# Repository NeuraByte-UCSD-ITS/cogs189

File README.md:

# **COGS 189 - BCI Project**  

This repository contains the code for our **COGS 189 Brain-Computer Interface (BCI) experiment**, where we map **action-based EEG signals and SSVEP** to real-time cursor control.  

### **Project Structure**  
- **`online` branch**: Handles real-time BCI implementation and cursor control mapping.  
- **`offline` branch**: Focuses on EEG signal preprocessing, transformation, and classification.  

### **Getting Started**  
1. Clone the repository:  
   ```bash
   git clone https://github.com/NeuraByte-UCSD-ITS/cogs189.git
   ```
2. Switch to the relevant branch:  
   ```bash
   git checkout online   # or git checkout offline
   ```
3. Stay updated with the latest changes:  
   ```bash
   git pull origin branch-name  # Replace 'branch-name' with online/offline/main
   ```

### **Contributing**  
1. Make changes and push to your branch:  
   ```bash
   git add .
   git commit -m "Your commit message"
   git push origin branch-name
   ```
2. Submit a pull request on GitHub to merge into `main`.  
3. Keep documentation updated for reproducibility.  

### **Team Members**  

| Name                  | PID        | Email             | Discord            | GitHub Username |
|-----------------------|-----------|-------------------|--------------------|-----------------|
| **Edwin Ruiz**        | A17136339 | e1ruiz@ucsd.edu   | ucsd_its_neuro     | NeuraByte-UCSD-ITS |
| **Vishal Patel**      | v7patel    | v7patel@ucsd.edu  | vishalp            | vip11017 |
| **Dante Testini**     | A16772108 | dtestini@ucsd.edu | dante.___          | Dante-t0 |
| **Nancy Shen**        | A17006379 | nshen@ucsd.edu    | nyzll              | nancyshenn |
| **Sarah R. Bulatao**  | A17239438 | sbulatao@ucsd.edu | 3ffulgentx#4449    | sbulatao |
| **Andy Huang**        | A17391626 | anh031@ucsd.edu   | nub6234            | anh1231 |

### **Project Resources**  

📄 **Team Documents (Proposal, Contract, Research Notes)**  
[**Google Docs - COGS 189 Team Documents**](https://docs.google.com/document/d/1kmoATubGGtCyLEcY0Lt7Y57b31m-O8rysbtMINhthrM/edit?usp=sharing)  

🌐 **Project Website (Introduction, Methods, Results)**  
[**Google Sites - COGS 189 BCI Project**](https://sites.google.com/d/1s-25WKa0uhgr7BEy_yGSoqZ5aTbzqCl3/p/1npJnzpZkbIYuBNoyv4HmWuREFpSlRTLe/edit?pli=1&authuser=2)

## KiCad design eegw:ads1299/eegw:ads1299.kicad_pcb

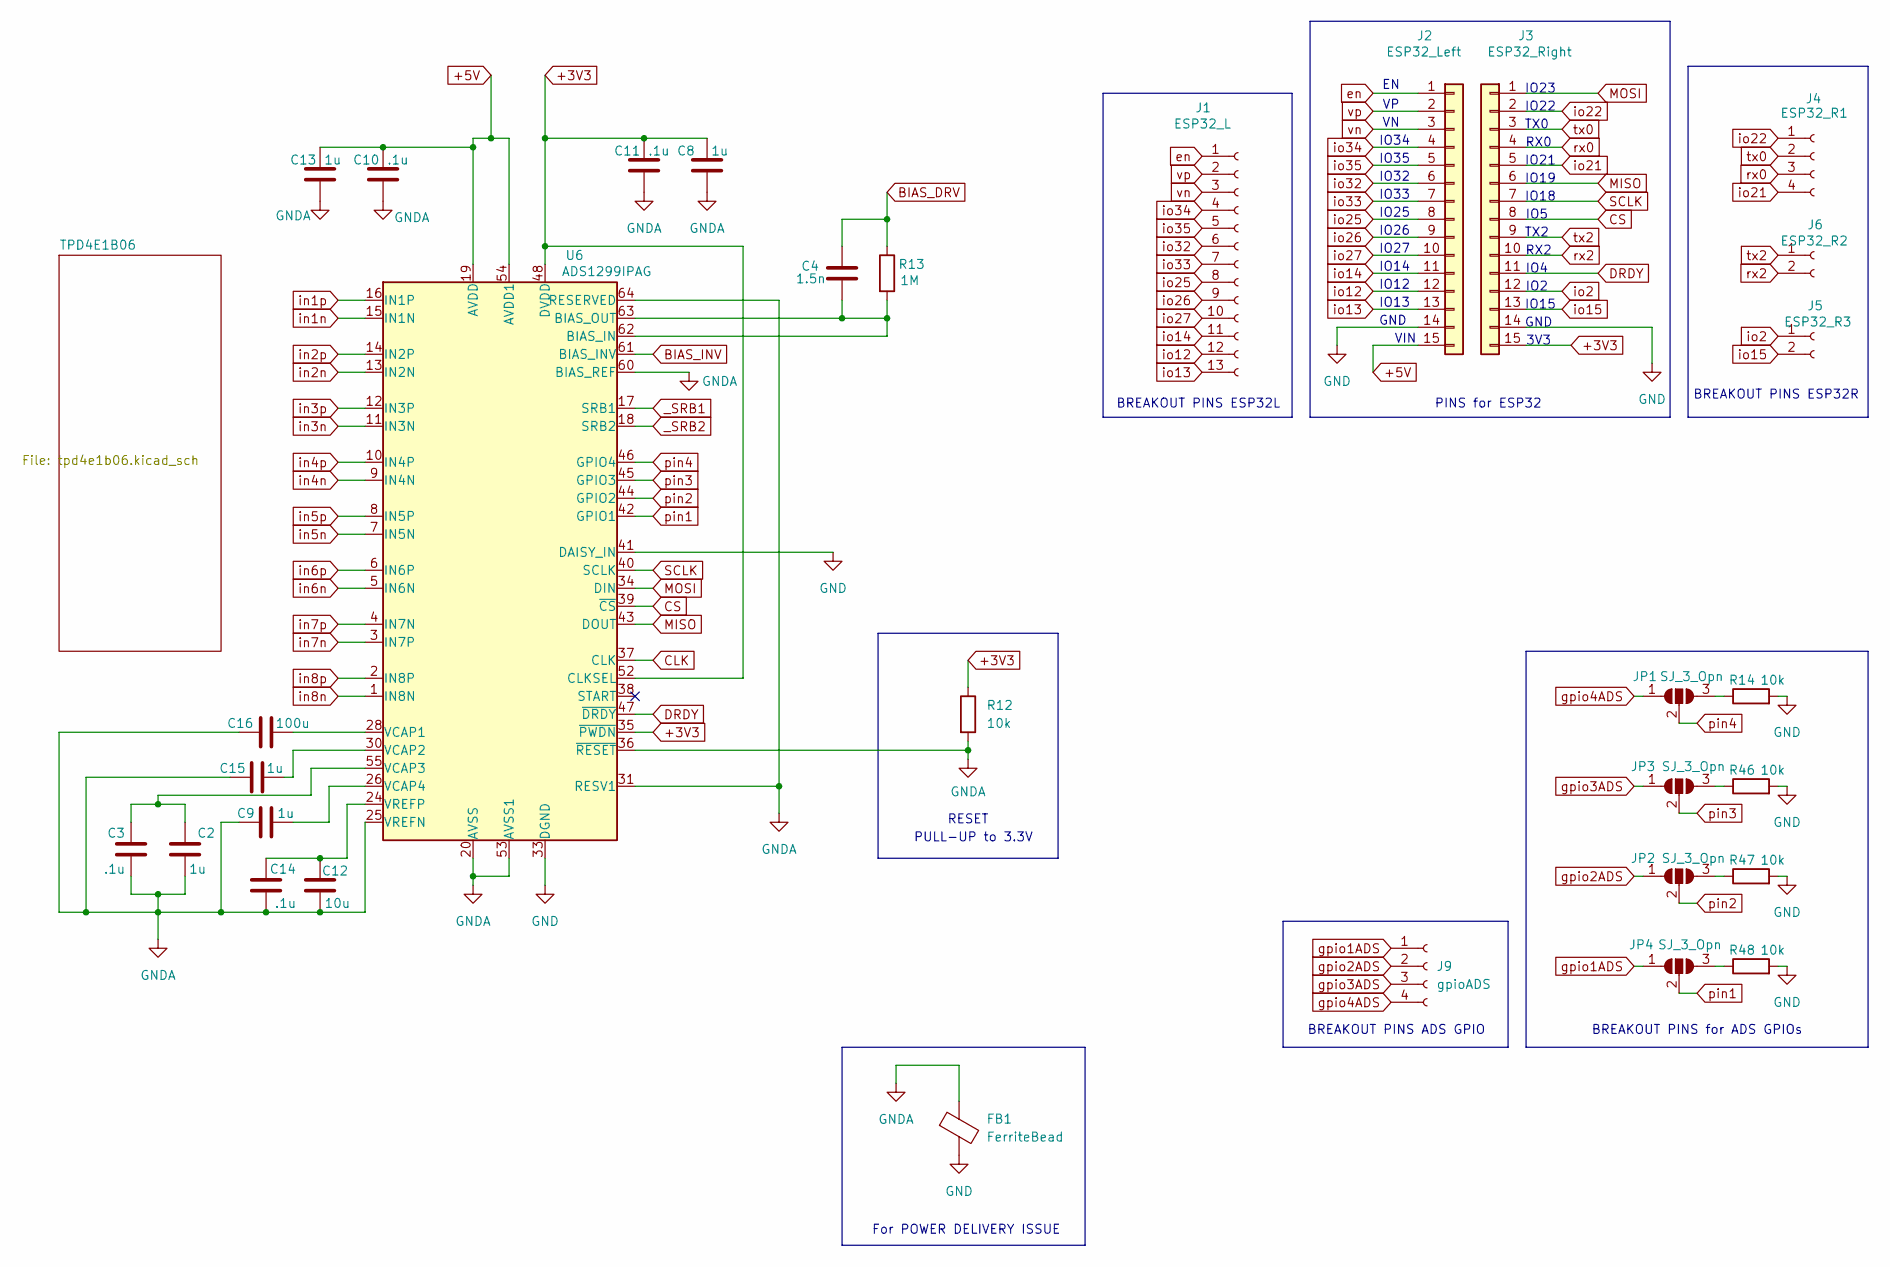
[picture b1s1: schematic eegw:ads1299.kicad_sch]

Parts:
C2, C8, C9, C13, C15: 1u; C_0603_1608Metric
C3, C10, C11, C14: .1u; C_0603_1608Metric
C4: 1.5n; C_0603_1608Metric
C12: 10u; C_0603_1608Metric
C16: 100u; C_0603_1608Metric
FB1: FerriteBead; L_0603_1608Metric
J1: ESP32_L; PinSocket_1x13_P2.54mm_Vertical
J2: ESP32_Left; PinSocket_1x15_P2.54mm_Vertical
J3: ESP32_Right; PinSocket_1x15_P2.54mm_Vertical
J4: ESP32_R1; PinSocket_1x04_P2.54mm_Vertical
J5: ESP32_R3; PinSocket_1x02_P2.54mm_Vertical
J6: ESP32_R2; PinSocket_1x02_P2.54mm_Vertical
J9: gpioADS; PinSocket_1x04_P2.54mm_Vertical
JP1, JP2, JP3, JP4: SJ_3_Opn; SolderJumper-3_P1.3mm_Open_RoundedPad1.0x1.5mm_NumberLabels
R12, R14, R46, R47, R48: 10k; R_0603_1608Metric
R13: 1M; R_0603_1608Metric
U6: ADS1299IPAG; TQFP-64_10x10mm_P0.5mm

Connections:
+3V3: C8.1, C11.1, J3.15, R12.1, U6.35 (~PWDN), U6.48 (DVDD), U6.50 (DVDD), U6.52 (CLKSEL)
+5V: C10.1, C13.1, J2.15, U6.19 (AVDD), U6.21 (AVDD), U6.22 (AVDD), U6.54 (AVDD1), U6.56 (AVDD), U6.59 (AVDD); also elsewhere on the board
BIAS_DRV: C4.1, R13.1; also elsewhere on the board
BIAS_INV: U6.61 (BIAS_INV)
CLK: U6.37 (CLK)
CS: J3.8, U6.39 (~CS)
DRDY: J3.11, U6.47 (~DRDY)
GND: FB1.2, J2.14, J3.14, R14.2, R46.2, R47.2, R48.2, U6.33 (DGND), U6.41 (DAISY_IN), U6.49 (DGND), U6.51 (DGND)
GNDA: C2.1, C3.1, C8.2, C9.1, C10.2, C11.2, C12.1, C13.2, C14.1, C15.1, C16.2, FB1.1, R12.2, U6.20 (AVSS), U6.23 (AVSS), U6.25 (VREFN), U6.31 (RESV1), U6.32 (AVSS), U6.36 (~RESET), U6.53 (AVSS1), U6.57 (AVSS), U6.58 (AVSS), U6.60 (BIAS_REF), U6.64 (RESERVED); also elsewhere on the board
MISO: J3.6, U6.43 (DOUT)
MOSI: J3.1, U6.34 (DIN)
unnamed: JP1.3 (B), R14.1
unnamed: JP2.3 (B), R47.1
unnamed: JP3.3 (B), R46.1
unnamed: JP4.3 (B), R48.1
unnamed: C4.2, R13.2, U6.62 (BIAS_IN), U6.63 (BIAS_OUT)
unnamed: C16.1, U6.28 (VCAP1)
unnamed: C15.2, U6.30 (VCAP2)
unnamed: C2.2, C3.2, U6.55 (VCAP3)
unnamed: C9.2, U6.26 (VCAP4)
unnamed: C12.2, C14.2, U6.24 (VREFP)
SCLK: J3.7, U6.40 (SCLK)
_SRB1: U6.17 (SRB1); also elsewhere on the board
_SRB2: U6.18 (SRB2); also elsewhere on the board
en: J1.1, J2.1
gpio1ADS: J9.1, JP4.1 (A)
gpio2ADS: J9.2, JP2.1 (A)
gpio3ADS: J9.3, JP3.1 (A)
gpio4ADS: J9.4, JP1.1 (A)
in1n: U6.15 (IN1N); also elsewhere on the board
in1p: U6.16 (IN1P); also elsewhere on the board
in2n: U6.13 (IN2N); also elsewhere on the board
in2p: U6.14 (IN2P); also elsewhere on the board
in3n: U6.11 (IN3N); also elsewhere on the board
in3p: U6.12 (IN3P); also elsewhere on the board
in4n: U6.9 (IN4N); also elsewhere on the board
in4p: U6.10 (IN4P); also elsewhere on the board
in5n: U6.7 (IN5N); also elsewhere on the board
in5p: U6.8 (IN5P); also elsewhere on the board
in6n: U6.5 (IN6N); also elsewhere on the board
in6p: U6.6 (IN6P); also elsewhere on the board
in7n: U6.3 (IN7P); also elsewhere on the board
in7p: U6.4 (IN7N); also elsewhere on the board
in8n: U6.1 (IN8N); also elsewhere on the board
in8p: U6.2 (IN8P); also elsewhere on the board
io2: J3.12, J5.1
io12: J1.12, J2.12
io13: J1.13, J2.13
io14: J1.11, J2.11
io15: J3.13, J5.2
io21: J3.5, J4.4
io22: J3.2, J4.1
io25: J1.8, J2.8
io26: J1.9, J2.9
io27: J1.10, J2.10
io32: J1.6, J2.6
io33: J1.7, J2.7
io34: J1.4, J2.4
io35: J1.5, J2.5
pin1: JP4.2 (C), U6.42 (GPIO1)
pin2: JP2.2 (C), U6.44 (GPIO2)
pin3: JP3.2 (C), U6.45 (GPIO3)
pin4: JP1.2 (C), U6.46 (GPIO4)
rx0: J3.4, J4.3
rx2: J3.10, J6.2
tx0: J3.3, J4.2
tx2: J3.9, J6.1
vn: J1.3, J2.3
vp: J1.2, J2.2

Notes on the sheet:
IO19
IO21
IO4
For POWER DELIVERY ISSUE
IO15
IO34
IO33
IO26
PINS for ESP32
TX0
BREAKOUT PINS ESP32R
IO2
IO18
IO27
BREAKOUT PINS ESP32L
TX2
IO13
IO25
GND
BREAKOUT PINS for ADS GPIOs
IO32
IO22
RX0
IO23
RESET
IO35
PULL-UP to 3.3V
VIN
IO14
IO5
BREAKOUT PINS ADS GPIO
3V3
RX2
IO12

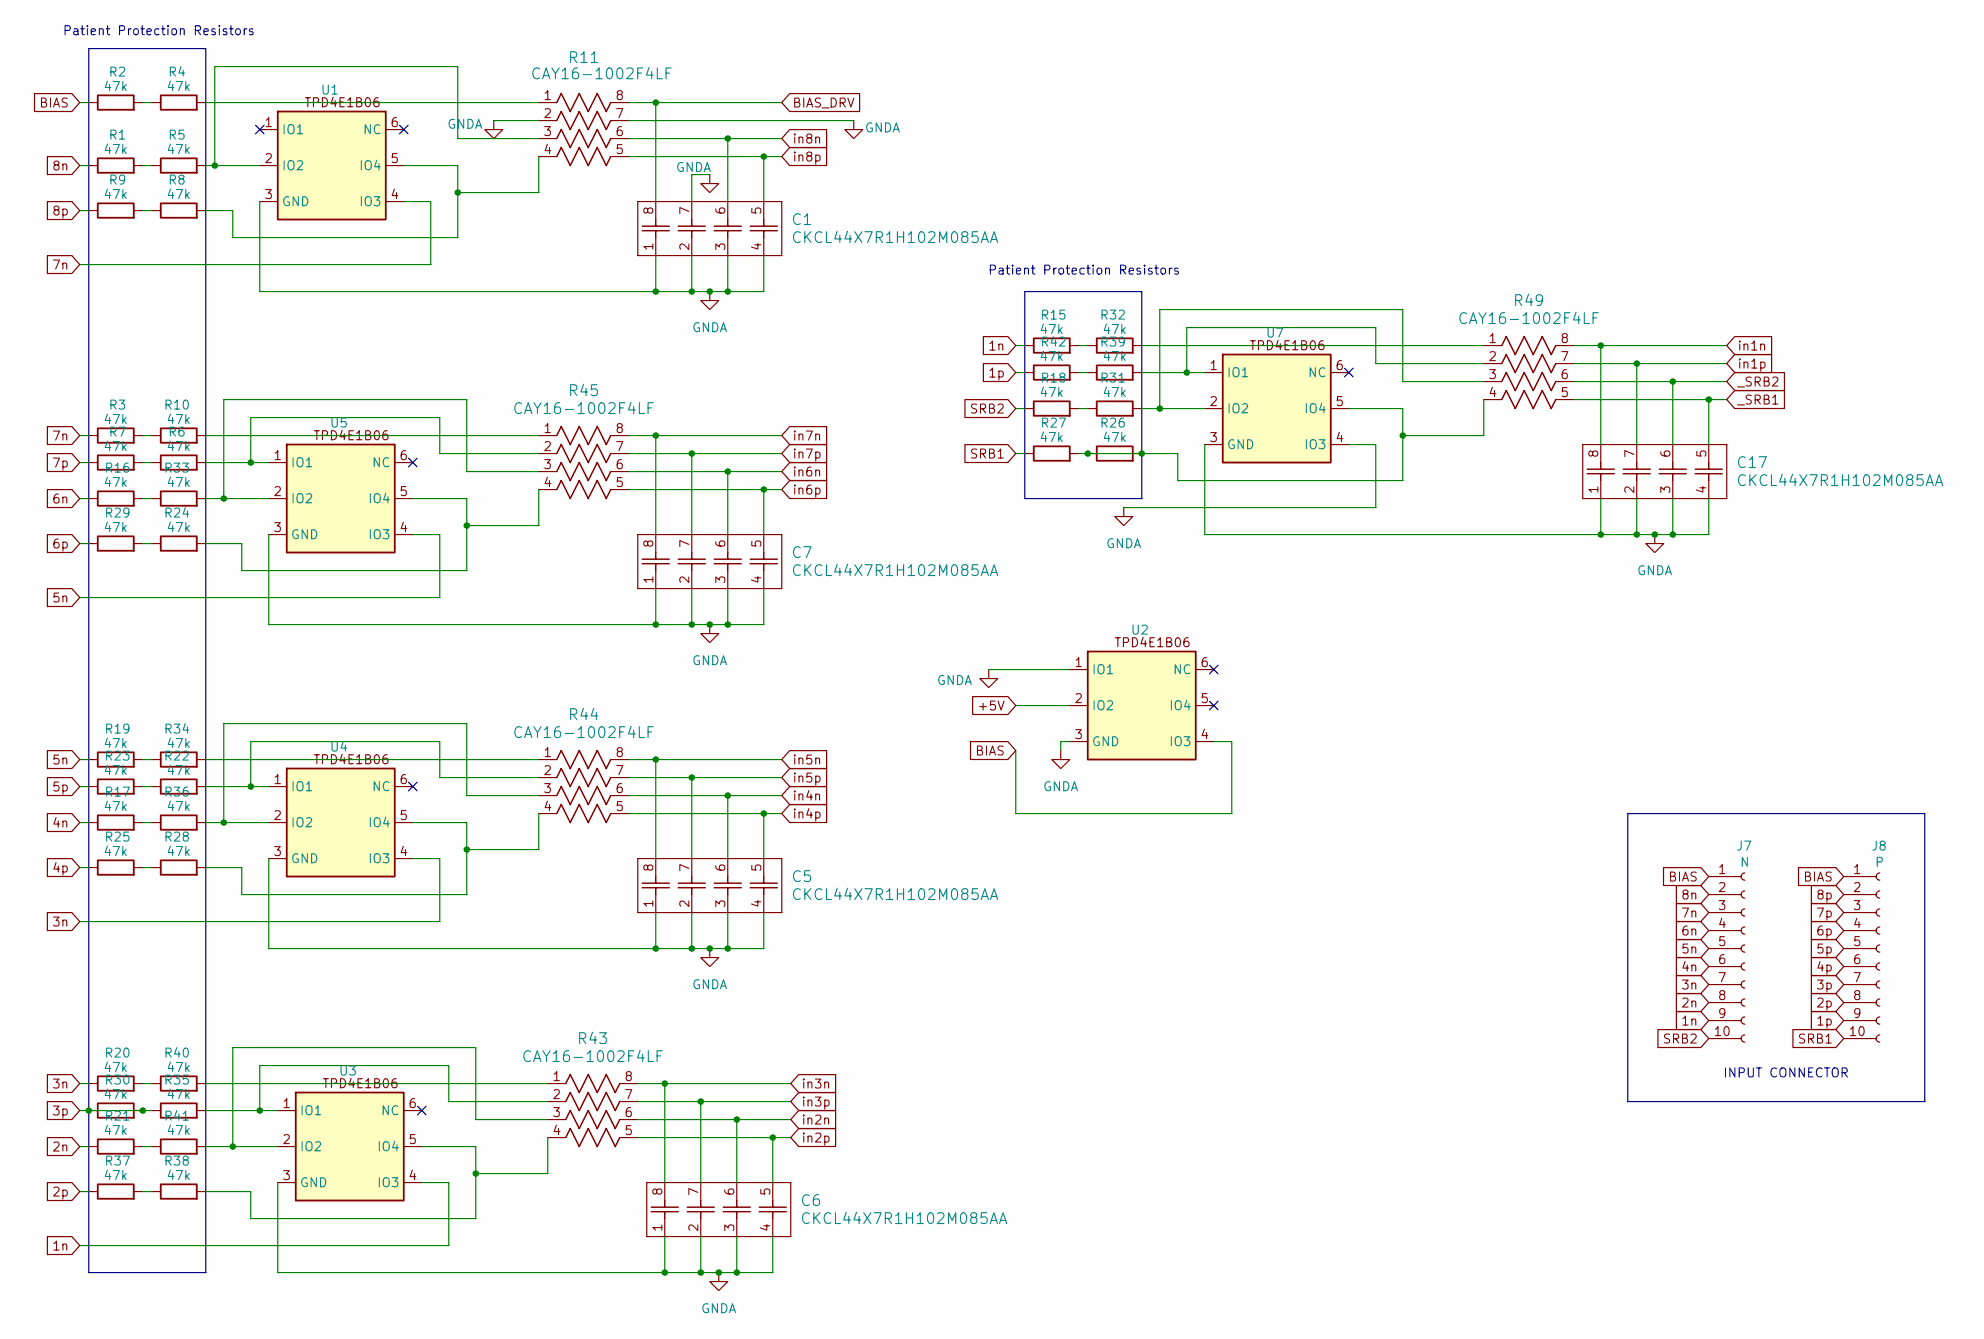
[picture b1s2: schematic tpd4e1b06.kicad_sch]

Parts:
C1, C5, C6, C7, C17: CKCL44X7R1H102M085AA; CKCL44_TDK
J7: N; PinSocket_1x10_P2.54mm_Vertical
J8: P; PinSocket_1x10_P2.54mm_Vertical
R1, R2, R3, R4, R5, R6, R7, R8, R9, R10, R15, R16, R17, R18, R19, R20, R21, R22, R23, R24, R25, R26, R27, R28, R29, R30, R31, R32, R33, R34, R35, R36, R37, R38, R39, R40, R41, R42: 47k; R_0603_1608Metric
R11, R43, R44, R45, R49: CAY16-1002F4LF; BO_CAY16
U1, U2, U3, U4, U5, U7: SOT-363_SC-70-6

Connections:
1n: J7.9, R15.1, U3.4 (IO3)
1p: J8.9, R42.1
2n: J7.8, R21.1
2p: J8.8, R37.1
3n: J7.7, R20.1, U4.4 (IO3)
3p: J8.7, R30.1, R30.2, R35.1
4n: J7.6, R17.1
4p: J8.6, R25.1
5n: J7.5, R19.1, U5.4 (IO3)
5p: J8.5, R23.1
6n: J7.4, R16.1
6p: J8.4, R29.1
7n: J7.3, R3.1, U1.4 (IO3)
7p: J8.3, R7.1
8n: J7.2, R1.1
8p: J8.2, R9.1
+5V: U2.2 (IO2); also elsewhere on the board
BIAS: J7.1, J8.1, R2.1, U2.4 (IO3)
BIAS_DRV: C1.8, R11.8; also elsewhere on the board
GNDA: C1.1, C1.2, C1.3, C1.4, C1.7, C5.1, C5.2, C5.3, C5.4, C6.1, C6.2, C6.3, C6.4, C7.1, C7.2, C7.3, C7.4, C17.1, C17.2, C17.3, C17.4, R11.2, R11.7, U1.3 (GND), U2.1 (IO1), U2.3 (GND), U3.3 (GND), U4.3 (GND), U5.3 (GND), U7.3 (GND), U7.4 (IO3); also elsewhere on the board
unnamed: R1.2, R5.1
unnamed: R2.2, R4.1
unnamed: R6.1, R7.2
unnamed: R8.1, R9.2
unnamed: R3.2, R10.1
unnamed: R10.2, R45.1
unnamed: R4.2, R11.1
unnamed: R15.2, R32.1
unnamed: R16.2, R33.1
unnamed: R17.2, R36.1
unnamed: R18.2, R31.1
unnamed: R19.2, R34.1
unnamed: R20.2, R40.1
unnamed: R21.2, R41.1
unnamed: R22.1, R23.2
unnamed: R24.1, R29.2
unnamed: R25.2, R28.1
unnamed: R32.2, R49.1
unnamed: R34.2, R44.1
unnamed: R37.2, R38.1
unnamed: R39.1, R42.2
unnamed: R40.2, R43.1
unnamed: R5.2, R11.3, U1.2 (IO2)
unnamed: R8.2, R11.4, U1.5 (IO4)
unnamed: R35.2, R43.2, U3.1 (IO1)
unnamed: R41.2, R43.3, U3.2 (IO2)
unnamed: R38.2, R43.4, U3.5 (IO4)
unnamed: R22.2, R44.2, U4.1 (IO1)
unnamed: R36.2, R44.3, U4.2 (IO2)
unnamed: R28.2, R44.4, U4.5 (IO4)
unnamed: R6.2, R45.2, U5.1 (IO1)
unnamed: R33.2, R45.3, U5.2 (IO2)
unnamed: R24.2, R45.4, U5.5 (IO4)
unnamed: R39.2, R49.2, U7.1 (IO1)
unnamed: R31.2, R49.3, U7.2 (IO2)
unnamed: R26.1, R26.2, R27.2, R49.4, U7.5 (IO4)
SRB1: J8.10, R27.1
SRB2: J7.10, R18.1
_SRB1: C17.5, R49.5; also elsewhere on the board
_SRB2: C17.6, R49.6; also elsewhere on the board
in1n: C17.8, R49.8; also elsewhere on the board
in1p: C17.7, R49.7; also elsewhere on the board
in2n: C6.6, R43.6; also elsewhere on the board
in2p: C6.5, R43.5; also elsewhere on the board
in3n: C6.8, R43.8; also elsewhere on the board
in3p: C6.7, R43.7; also elsewhere on the board
in4n: C5.6, R44.6; also elsewhere on the board
in4p: C5.5, R44.5; also elsewhere on the board
in5n: C5.8, R44.8; also elsewhere on the board
in5p: C5.7, R44.7; also elsewhere on the board
in6n: C7.6, R45.6; also elsewhere on the board
in6p: C7.5, R45.5; also elsewhere on the board
in7n: C7.8, R45.8; also elsewhere on the board
in7p: C7.7, R45.7; also elsewhere on the board
in8n: C1.6, R11.6; also elsewhere on the board
in8p: C1.5, R11.5; also elsewhere on the board

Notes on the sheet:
Patient Protection Resistors
INPUT CONNECTOR

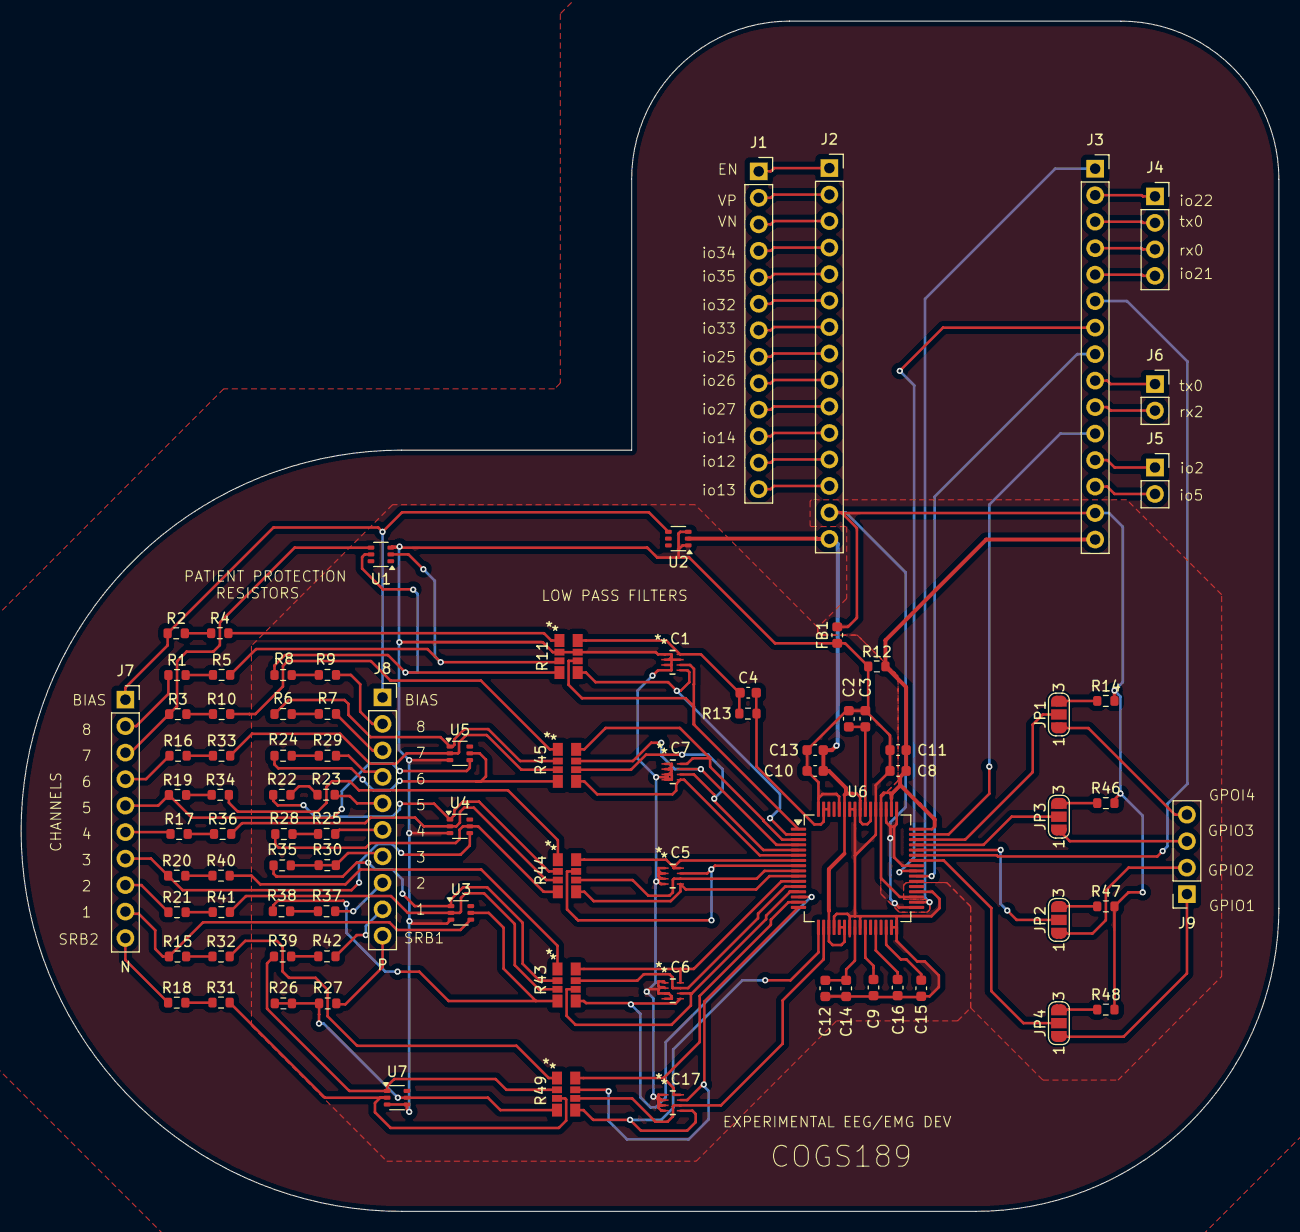
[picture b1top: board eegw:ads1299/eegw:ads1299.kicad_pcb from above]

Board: 2 copper layers, 120.6 x 114.1 mm, 87 parts (0 on the bottom side), 122 nets.

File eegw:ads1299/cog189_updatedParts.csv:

"Reference","Value","Datasheet","Footprint","Qty","DNP"
"C1,C5,C6,C7,C17","CKCL44X7R1H102M085AA","CKCL44X7R1H102M085AA","Capacitor_SMD:CKCL44_TDK","5",""
"C2,C8,C9,C13,C15","1u","~","Capacitor_SMD:C_0603_1608Metric","5",""
"C3,C10,C11,C14",".1u","~","Capacitor_SMD:C_0603_1608Metric","4",""
"C4","1.5n","~","Capacitor_SMD:C_0603_1608Metric","1",""
"C12","10u","~","Capacitor_SMD:C_0603_1608Metric","1",""
"C16","100u","~","Capacitor_SMD:CAPC_2012X145N Metric","1",""
"FB1","FerriteBead","~","Inductor_SMD:L_0603_1608Metric","1",""
"J1","ESP32_L","~","Connector_PinSocket_2.54mm:PinSocket_1x13_P2.54mm_Vertical","1",""
"J2","ESP32_Left","~","Connector_PinSocket_2.54mm:PinSocket_1x15_P2.54mm_Vertical","1",""
"J3","ESP32_Right","~","Connector_PinSocket_2.54mm:PinSocket_1x15_P2.54mm_Vertical","1",""
"J4","ESP32_R1","~","Connector_PinSocket_2.54mm:PinSocket_1x04_P2.54mm_Vertical","1",""
"J5","ESP32_R3","~","Connector_PinSocket_2.54mm:PinSocket_1x02_P2.54mm_Vertical","1",""
"J6","ESP32_R2","~","Connector_PinSocket_2.54mm:PinSocket_1x02_P2.54mm_Vertical","1",""
"J7","N","~","Connector_PinSocket_2.54mm:PinSocket_1x10_P2.54mm_Vertical","1",""
"J8","P","~","Connector_PinSocket_2.54mm:PinSocket_1x10_P2.54mm_Vertical","1",""
"J9","gpioADS","~","Connector_PinSocket_2.54mm:PinSocket_1x04_P2.54mm_Vertical","1",""
"R1,R2,R3,R4,R5,R6,R7,R8,R9,R10,R15,R16,R17,R18,R19,R20,R21,R22,R23,R24,R25,R26,R27,R28,R29,R30,R31,R32,R33,R34,R35,R36,R37,R38,R39,R40,R41,R42","47k","~","Resistor_SMD:R_0603_1608Metric","38",""
"R11,R43,R44,R45,R49","CAY16-1002F4LF","CAY16-1002F4LF","RF:BO_CAY16","5",""
"R12,R14,R46,R47,R48","10k","~","Resistor_SMD:R_0603_1608Metric","5",""
"R13","1M","~","Resistor_SMD:R_0603_1608Metric","1",""
"U1,U2,U3,U4,U5,U7","~","https://www.ti.com/lit/ds/symlink/tpd4e1b06.pdf?ts=173955177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","Package_TO_SOT_SMD:SOT-363_SC-70-6","6",""
"U6","ADS1299IPAG","https://www.ti.com/lit/ds/symlink/ads1299.pdf?ts=17389798611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","Package_QFP:TQFP-64_10x10mm_P0.5mm","1",""

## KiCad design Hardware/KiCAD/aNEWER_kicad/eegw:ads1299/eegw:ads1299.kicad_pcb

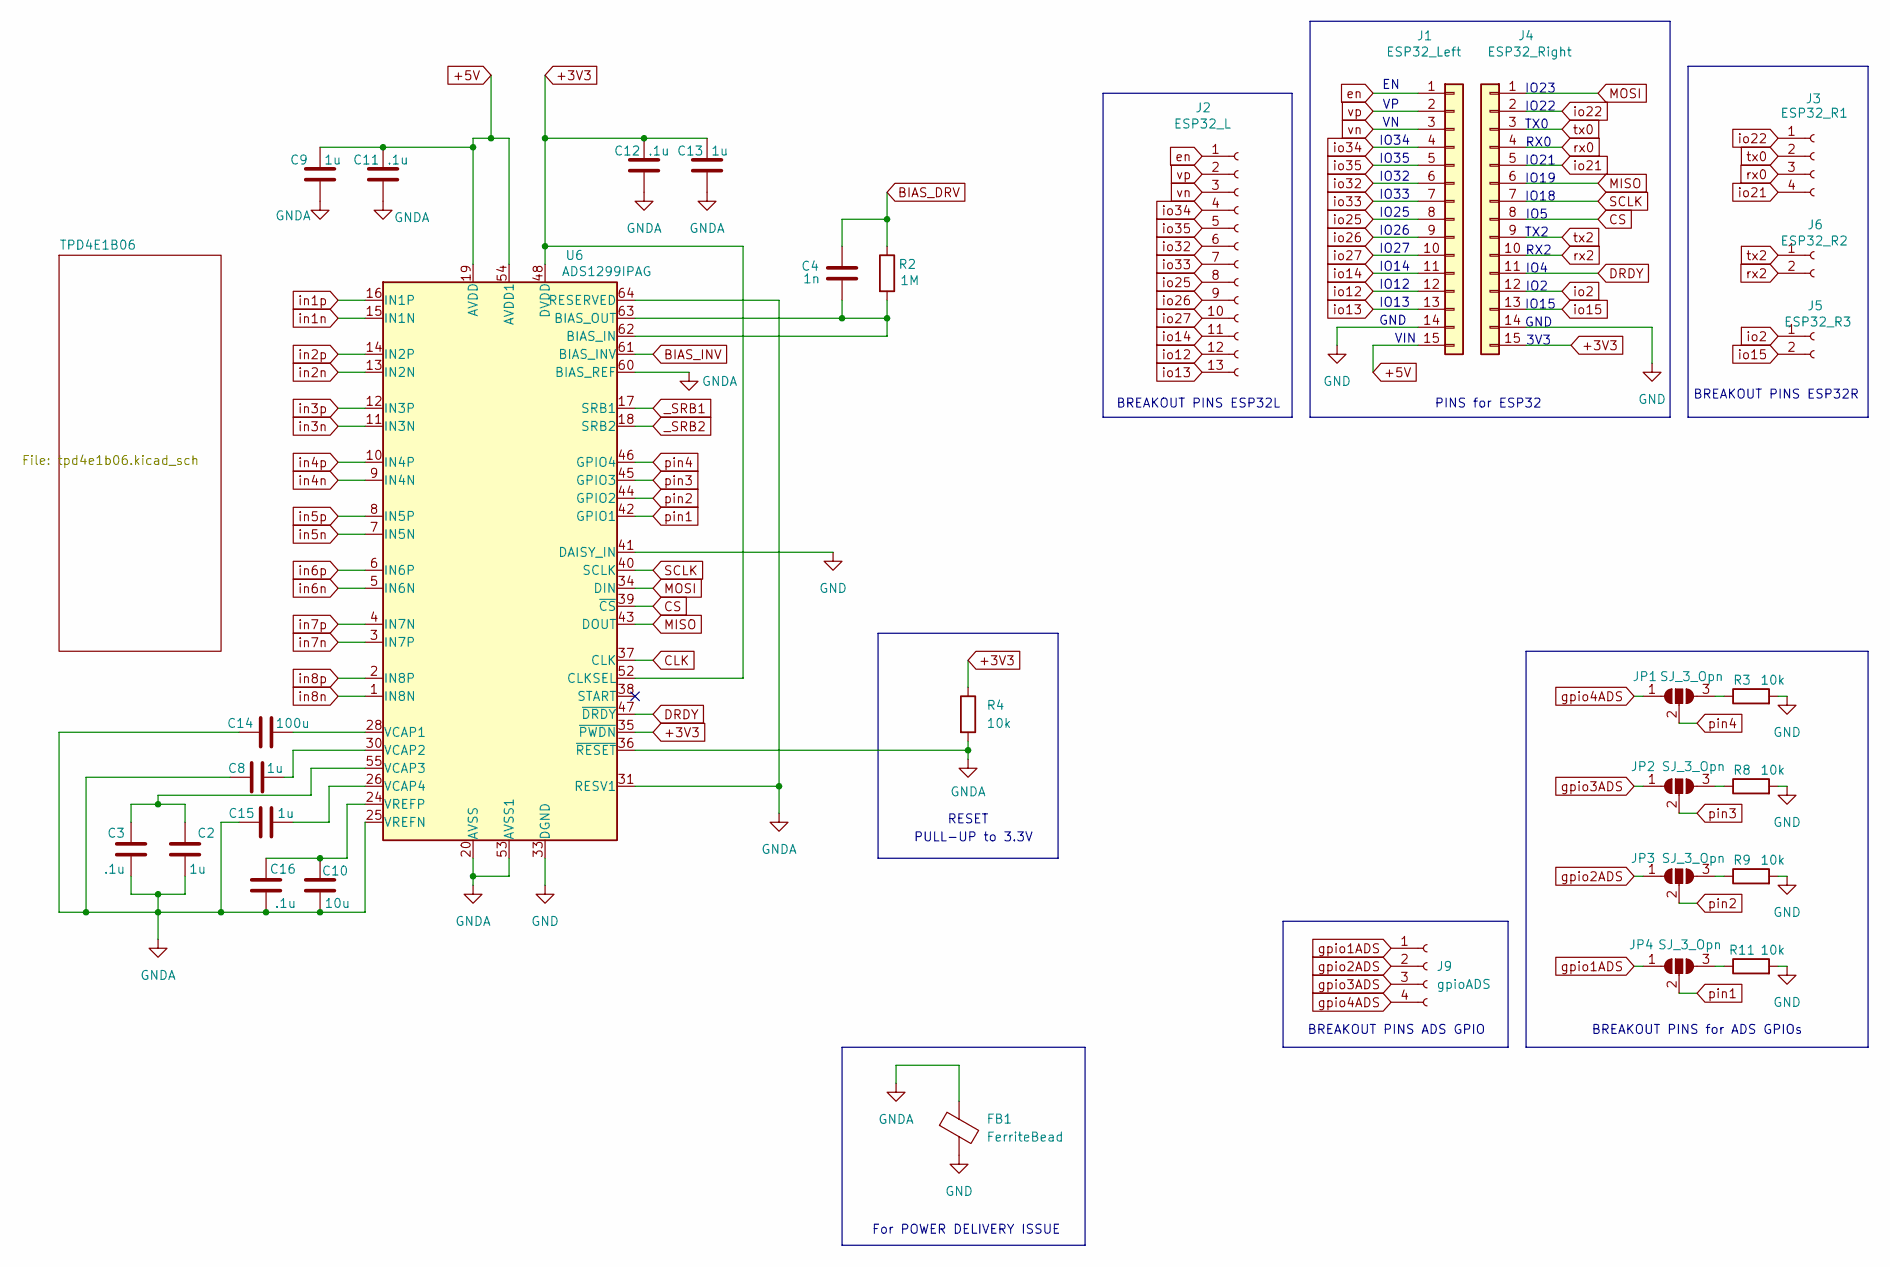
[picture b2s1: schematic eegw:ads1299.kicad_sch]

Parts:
C2, C8, C9, C13, C15: 1u; C_0603_1608Metric
C3, C11, C12, C16: .1u; C_0603_1608Metric
C4: 1n; C_0402_1005Metric
C10: 10u; C_0603_1608Metric
C14: 100u; CAPC_2012X145N Metric
FB1: FerriteBead; L_0603_1608Metric
J1: ESP32_Left; PinSocket_1x15_P2.54mm_Vertical
J2: ESP32_L; PinSocket_1x13_P2.54mm_Vertical
J3: ESP32_R1; PinSocket_1x04_P2.54mm_Vertical
J4: ESP32_Right; PinSocket_1x15_P2.54mm_Vertical
J5: ESP32_R3; PinSocket_1x02_P2.54mm_Vertical
J6: ESP32_R2; PinSocket_1x02_P2.54mm_Vertical
J9: gpioADS; PinSocket_1x04_P2.54mm_Vertical
JP1, JP2, JP3, JP4: SJ_3_Opn; SolderJumper-3_P1.3mm_Open_RoundedPad1.0x1.5mm_NumberLabels
R2: 1M; R_0603_1608Metric
R3, R4, R8, R9, R11: 10k; R_0603_1608Metric
U6: ADS1299IPAG; TQFP-64_10x10mm_P0.5mm

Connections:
+3V3: C12.1, C13.1, J4.15, R4.1, U6.35 (~PWDN), U6.48 (DVDD), U6.50 (DVDD), U6.52 (CLKSEL)
+5V: C9.1, C11.1, J1.15, U6.19 (AVDD), U6.21 (AVDD), U6.22 (AVDD), U6.54 (AVDD1), U6.56 (AVDD), U6.59 (AVDD); also elsewhere on the board
BIAS_DRV: C4.1, R2.1; also elsewhere on the board
BIAS_INV: U6.61 (BIAS_INV)
CLK: U6.37 (CLK)
CS: J4.8, U6.39 (~CS)
DRDY: J4.11, U6.47 (~DRDY)
GND: FB1.2, J1.14, J4.14, R3.2, R8.2, R9.2, R11.2, U6.33 (DGND), U6.41 (DAISY_IN), U6.49 (DGND), U6.51 (DGND)
GNDA: C2.1, C3.1, C8.1, C9.2, C10.1, C11.2, C12.2, C13.2, C14.2, C15.1, C16.1, FB1.1, R4.2, U6.20 (AVSS), U6.23 (AVSS), U6.25 (VREFN), U6.31 (RESV1), U6.32 (AVSS), U6.36 (~RESET), U6.53 (AVSS1), U6.57 (AVSS), U6.58 (AVSS), U6.60 (BIAS_REF), U6.64 (RESERVED); also elsewhere on the board
MISO: J4.6, U6.43 (DOUT)
MOSI: J4.1, U6.34 (DIN)
unnamed: JP1.3 (B), R3.1
unnamed: JP2.3 (B), R8.1
unnamed: JP3.3 (B), R9.1
unnamed: JP4.3 (B), R11.1
unnamed: C4.2, R2.2, U6.62 (BIAS_IN), U6.63 (BIAS_OUT)
unnamed: C14.1, U6.28 (VCAP1)
unnamed: C8.2, U6.30 (VCAP2)
unnamed: C2.2, C3.2, U6.55 (VCAP3)
unnamed: C15.2, U6.26 (VCAP4)
unnamed: C10.2, C16.2, U6.24 (VREFP)
SCLK: J4.7, U6.40 (SCLK)
_SRB1: U6.17 (SRB1); also elsewhere on the board
_SRB2: U6.18 (SRB2); also elsewhere on the board
en: J1.1, J2.1
gpio1ADS: J9.1, JP4.1 (A)
gpio2ADS: J9.2, JP3.1 (A)
gpio3ADS: J9.3, JP2.1 (A)
gpio4ADS: J9.4, JP1.1 (A)
in1n: U6.15 (IN1N); also elsewhere on the board
in1p: U6.16 (IN1P); also elsewhere on the board
in2n: U6.13 (IN2N); also elsewhere on the board
in2p: U6.14 (IN2P); also elsewhere on the board
in3n: U6.11 (IN3N); also elsewhere on the board
in3p: U6.12 (IN3P); also elsewhere on the board
in4n: U6.9 (IN4N); also elsewhere on the board
in4p: U6.10 (IN4P); also elsewhere on the board
in5n: U6.7 (IN5N); also elsewhere on the board
in5p: U6.8 (IN5P); also elsewhere on the board
in6n: U6.5 (IN6N); also elsewhere on the board
in6p: U6.6 (IN6P); also elsewhere on the board
in7n: U6.3 (IN7P); also elsewhere on the board
in7p: U6.4 (IN7N); also elsewhere on the board
in8n: U6.1 (IN8N); also elsewhere on the board
in8p: U6.2 (IN8P); also elsewhere on the board
io2: J4.12, J5.1
io12: J1.12, J2.12
io13: J1.13, J2.13
io14: J1.11, J2.11
io15: J4.13, J5.2
io21: J3.4, J4.5
io22: J3.1, J4.2
io25: J1.8, J2.8
io26: J1.9, J2.9
io27: J1.10, J2.10
io32: J1.6, J2.6
io33: J1.7, J2.7
io34: J1.4, J2.4
io35: J1.5, J2.5
pin1: JP4.2 (C), U6.42 (GPIO1)
pin2: JP3.2 (C), U6.44 (GPIO2)
pin3: JP2.2 (C), U6.45 (GPIO3)
pin4: JP1.2 (C), U6.46 (GPIO4)
rx0: J3.3, J4.4
rx2: J4.10, J6.2
tx0: J3.2, J4.3
tx2: J4.9, J6.1
vn: J1.3, J2.3
vp: J1.2, J2.2

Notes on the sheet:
IO19
IO21
IO4
For POWER DELIVERY ISSUE
IO15
IO34
IO33
IO26
PINS for ESP32
TX0
BREAKOUT PINS ESP32R
IO2
IO18
IO27
BREAKOUT PINS ESP32L
TX2
IO13
IO25
GND
BREAKOUT PINS for ADS GPIOs
IO32
IO22
RX0
IO23
RESET
IO35
PULL-UP to 3.3V
VIN
IO14
IO5
BREAKOUT PINS ADS GPIO
3V3
RX2
IO12

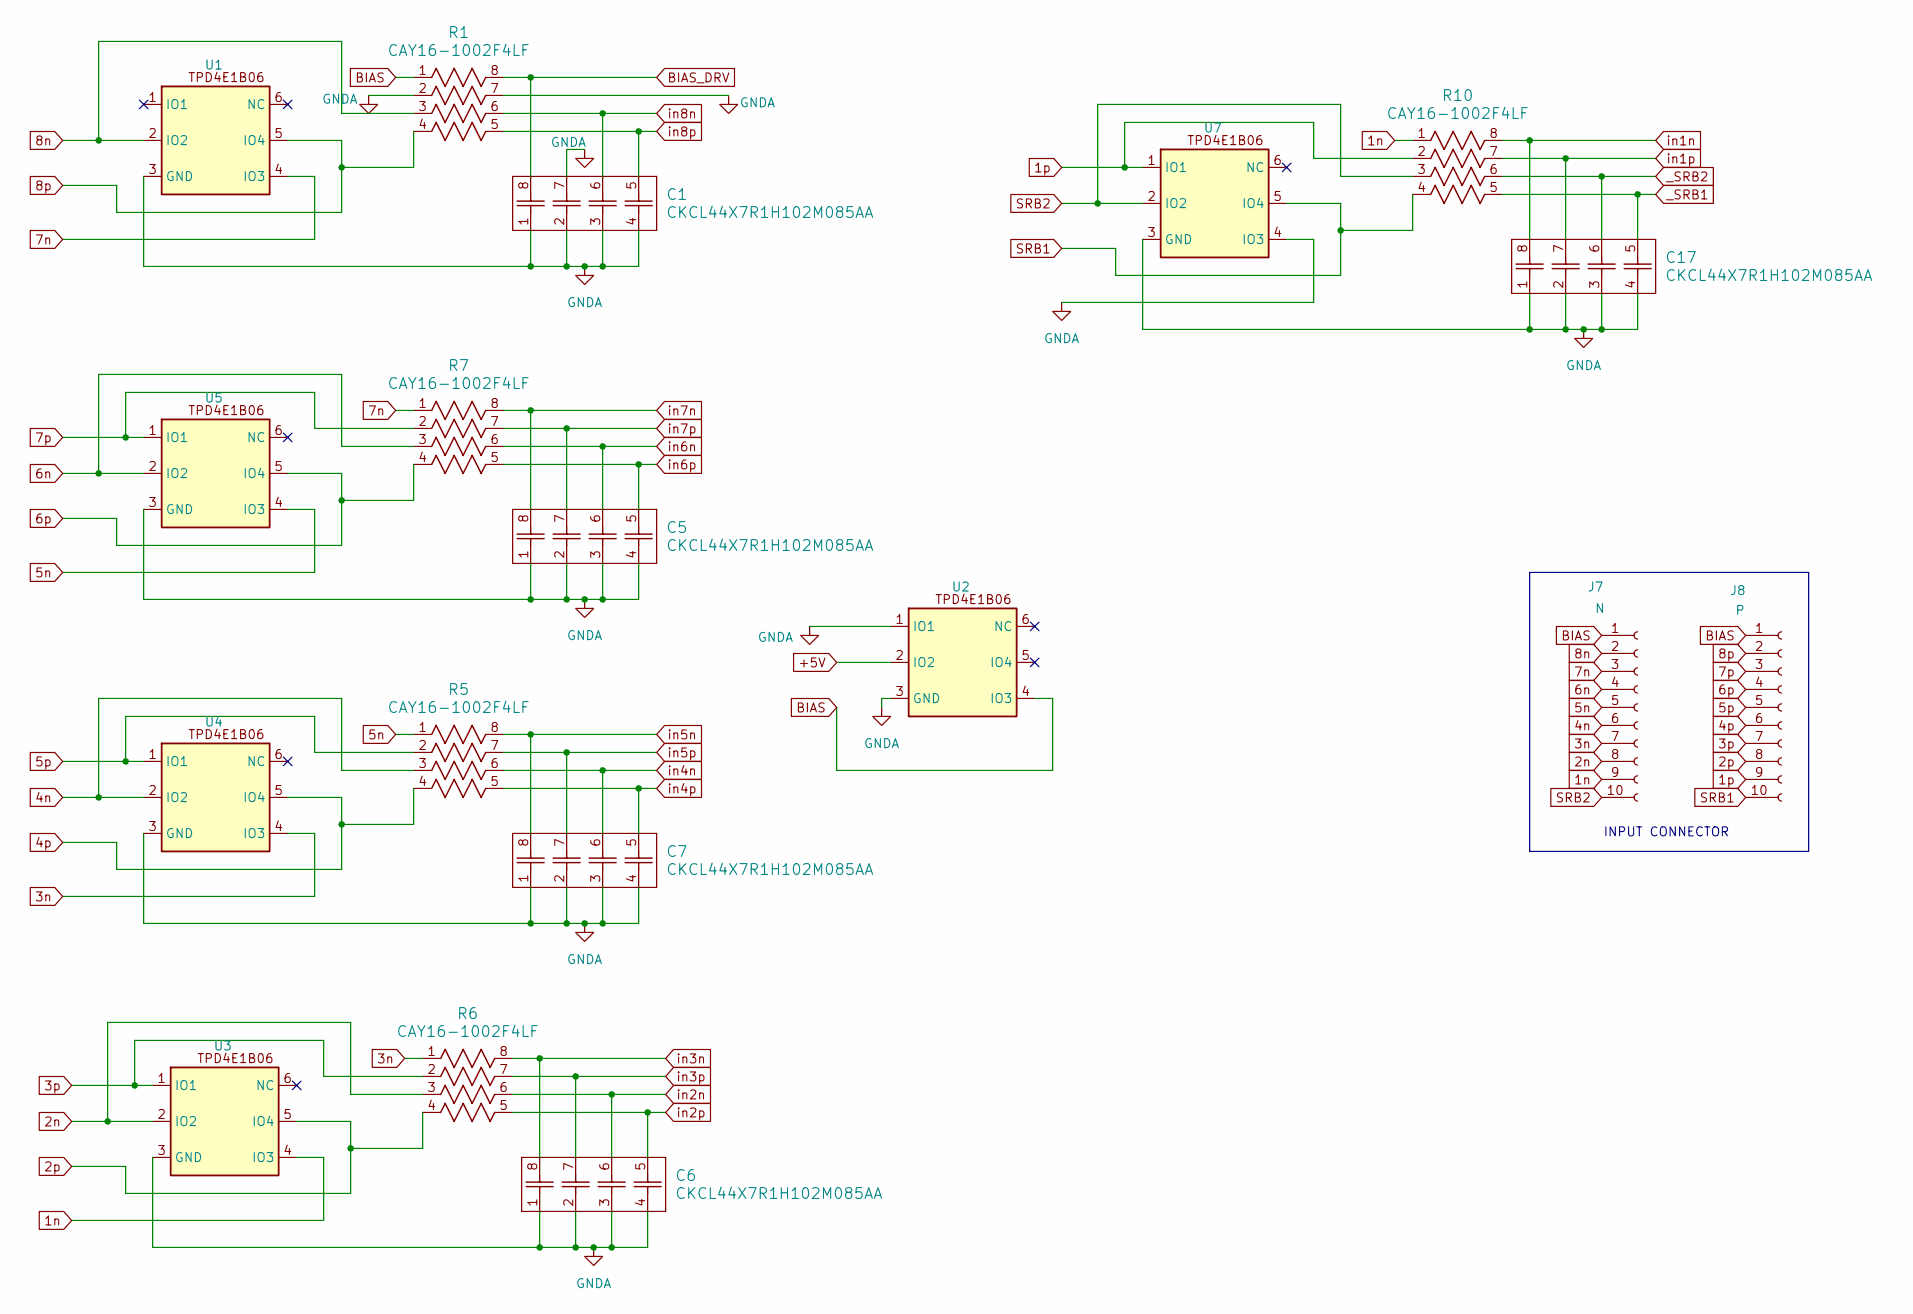
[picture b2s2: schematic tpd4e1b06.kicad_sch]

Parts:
C1, C5, C6, C7, C17: CKCL44X7R1H102M085AA; CKCL44_TDK
J7: N; PinSocket_1x10_P2.54mm_Vertical
J8: P; PinSocket_1x10_P2.54mm_Vertical
R1, R5, R6, R7, R10: CAY16-1002F4LF; BO_CAY16
U1, U2, U3, U4, U5, U7: SOT-363_SC-70-6

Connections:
1n: J7.9, R10.1, U3.4 (IO3)
1p: J8.9, R10.2, U7.1 (IO1)
2n: J7.8, R6.3, U3.2 (IO2)
2p: J8.8, R6.4, U3.5 (IO4)
3n: J7.7, R6.1, U4.4 (IO3)
3p: J8.7, R6.2, U3.1 (IO1)
4n: J7.6, R5.3, U4.2 (IO2)
4p: J8.6, R5.4, U4.5 (IO4)
5n: J7.5, R5.1, U5.4 (IO3)
5p: J8.5, R5.2, U4.1 (IO1)
6n: J7.4, R7.3, U5.2 (IO2)
6p: J8.4, R7.4, U5.5 (IO4)
7n: J7.3, R7.1, U1.4 (IO3)
7p: J8.3, R7.2, U5.1 (IO1)
8n: J7.2, R1.3, U1.2 (IO2)
8p: J8.2, R1.4, U1.5 (IO4)
+5V: U2.2 (IO2); also elsewhere on the board
BIAS: J7.1, J8.1, R1.1, U2.4 (IO3)
BIAS_DRV: C1.8, R1.8; also elsewhere on the board
GNDA: C1.1, C1.2, C1.3, C1.4, C1.7, C5.1, C5.2, C5.3, C5.4, C6.1, C6.2, C6.3, C6.4, C7.1, C7.2, C7.3, C7.4, C17.1, C17.2, C17.3, C17.4, R1.2, R1.7, U1.3 (GND), U2.1 (IO1), U2.3 (GND), U3.3 (GND), U4.3 (GND), U5.3 (GND), U7.3 (GND), U7.4 (IO3); also elsewhere on the board
SRB1: J8.10, R10.4, U7.5 (IO4)
SRB2: J7.10, R10.3, U7.2 (IO2)
_SRB1: C17.5, R10.5; also elsewhere on the board
_SRB2: C17.6, R10.6; also elsewhere on the board
in1n: C17.8, R10.8; also elsewhere on the board
in1p: C17.7, R10.7; also elsewhere on the board
in2n: C6.6, R6.6; also elsewhere on the board
in2p: C6.5, R6.5; also elsewhere on the board
in3n: C6.8, R6.8; also elsewhere on the board
in3p: C6.7, R6.7; also elsewhere on the board
in4n: C7.6, R5.6; also elsewhere on the board
in4p: C7.5, R5.5; also elsewhere on the board
in5n: C7.8, R5.8; also elsewhere on the board
in5p: C7.7, R5.7; also elsewhere on the board
in6n: C5.6, R7.6; also elsewhere on the board
in6p: C5.5, R7.5; also elsewhere on the board
in7n: C5.8, R7.8; also elsewhere on the board
in7p: C5.7, R7.7; also elsewhere on the board
in8n: C1.6, R1.6; also elsewhere on the board
in8p: C1.5, R1.5; also elsewhere on the board

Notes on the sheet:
INPUT CONNECTOR

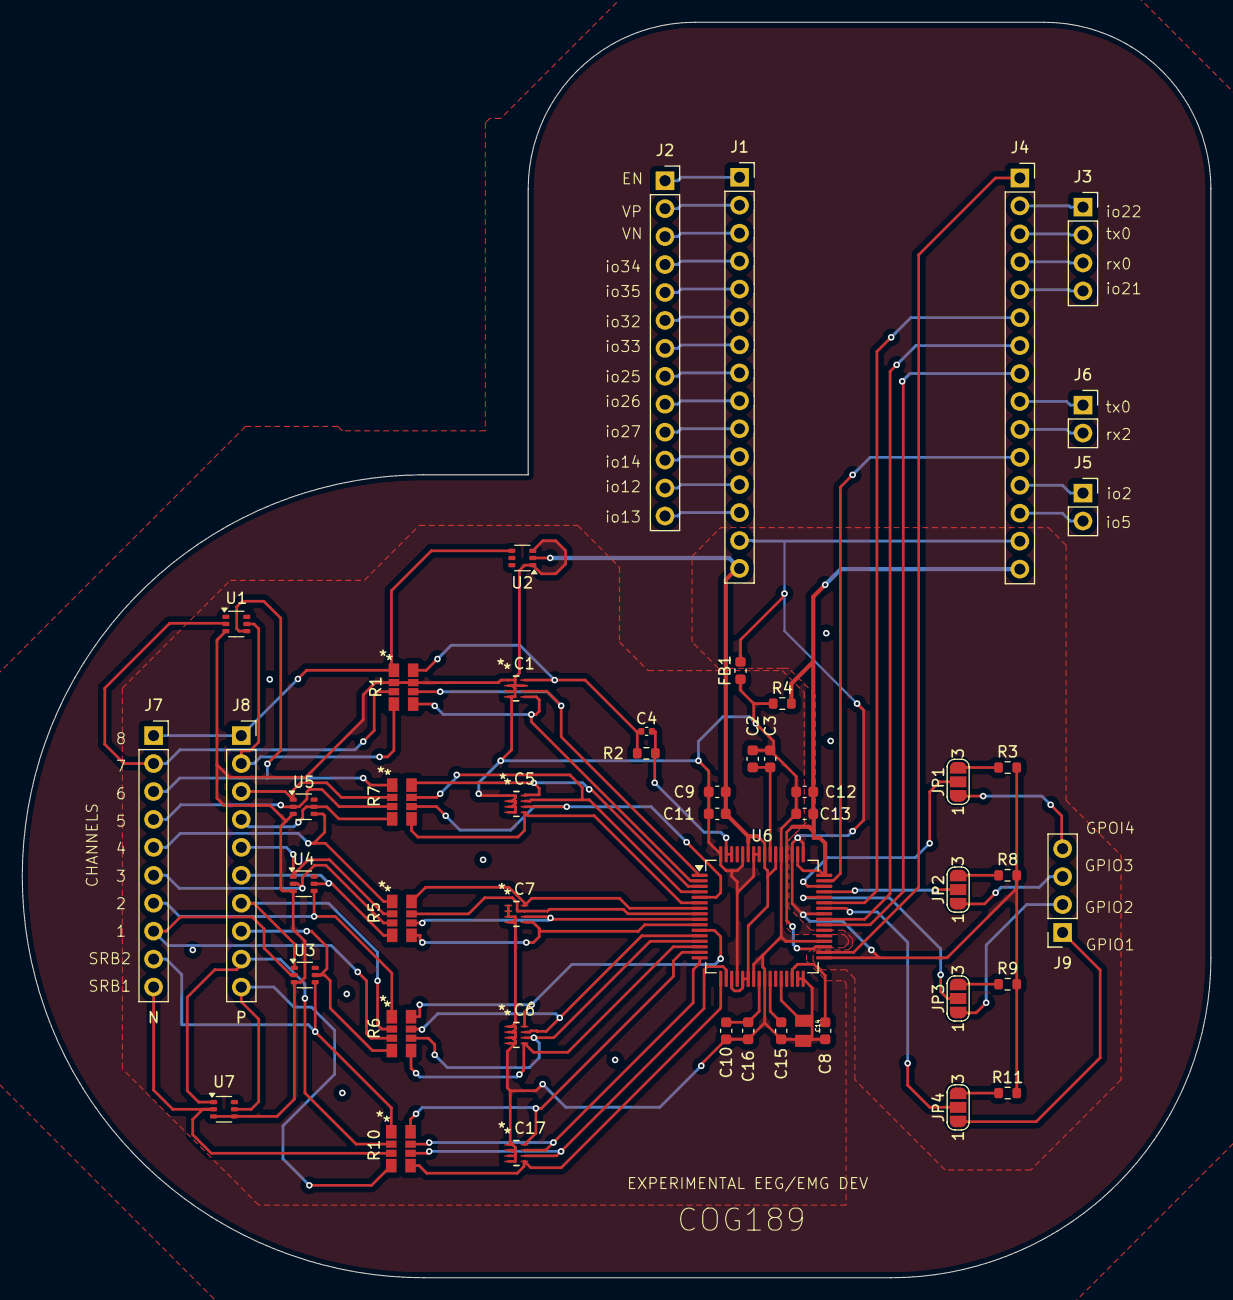
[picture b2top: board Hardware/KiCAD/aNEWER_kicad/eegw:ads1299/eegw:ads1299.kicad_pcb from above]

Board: 2 copper layers, 108.1 x 114.1 mm, 49 parts (0 on the bottom side), 86 nets.
